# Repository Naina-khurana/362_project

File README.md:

# ProtoPaw (ECE 362, Team 72)

Wearable glove (flex sensor + MPU6050) that drives a 3D-printed robotic finger with an MG90S servo, with live telemetry on the TFT LCD. Runs on the Purdue Proton (RP2350B), PlatformIO + Pico SDK.

## Layout

| File | What it does |
|---|---|
| `include/pins.h` | Shared pin map. Change pins here only |
| `src/flex.c` | ADC driver for the flex sensor |
| `src/servo.c` | PWM driver for the servo |
| `src/imu.c` | I2C driver for the MPU6050, pitch/roll with a complementary filter |
| `src/tft.c` | SPI display, wraps the course `lcd.c` library |
| `src/button.c` | GPIO mode button with debounce |
| `src/main.c` | Main loop, FLEX and TILT modes |

## TFT library setup

Copy `lcd.c` into `src/` and `lcd.h` into `include/` from the course project-lcd zip. In `lcd.c`, replace the three `x` defines with

```c
#include "pins.h"
#define CS_NUM    PIN_CS
#define DC_NUM    PIN_DC
#define RESET_NUM PIN_nRESET
```

Until those files are added, `tft.c` builds as empty stubs so everything else still runs.

## Pin map

| Device | Signal | Pin | Peripheral |
|---|---|---|---|
| Flex sensor | Divider midpoint | GP40 | ADC0 |
| MPU6050 | SDA / SCL | GP4 / GP5 | I2C0 |
| TFT LCD | SCK / SDI | GP10 / GP11 | SPI1 |
| TFT LCD | CS / DC / RESET | GP12 / GP13 / GP14 | GPIO |
| MG90S servo | Signal | GP16 | PWM slice 0A |
| Mode button | Onboard | GP21 | GPIO |

Do not use GP0/GP1 (debug UART), GP21/GP26 for SPI (button debounce circuitry), or GP22-25 (onboard LEDs) for anything else.

## Power

- Flex divider. 3V3 to flex sensor to GP40 to 47k to GND
- MPU6050. VIN to 3V3
- TFT. 3V3 with 10 uF + 0.1 uF caps at its power pins
- Servo. Separate 5V supply, grounds tied together

## Testing the ADC

Set `TEST_MODE_RAW_ADC` to 1 in `main.c`, upload, open the serial monitor and bend the sensor. The raw value should move smoothly and never sit at 0 or 4095.

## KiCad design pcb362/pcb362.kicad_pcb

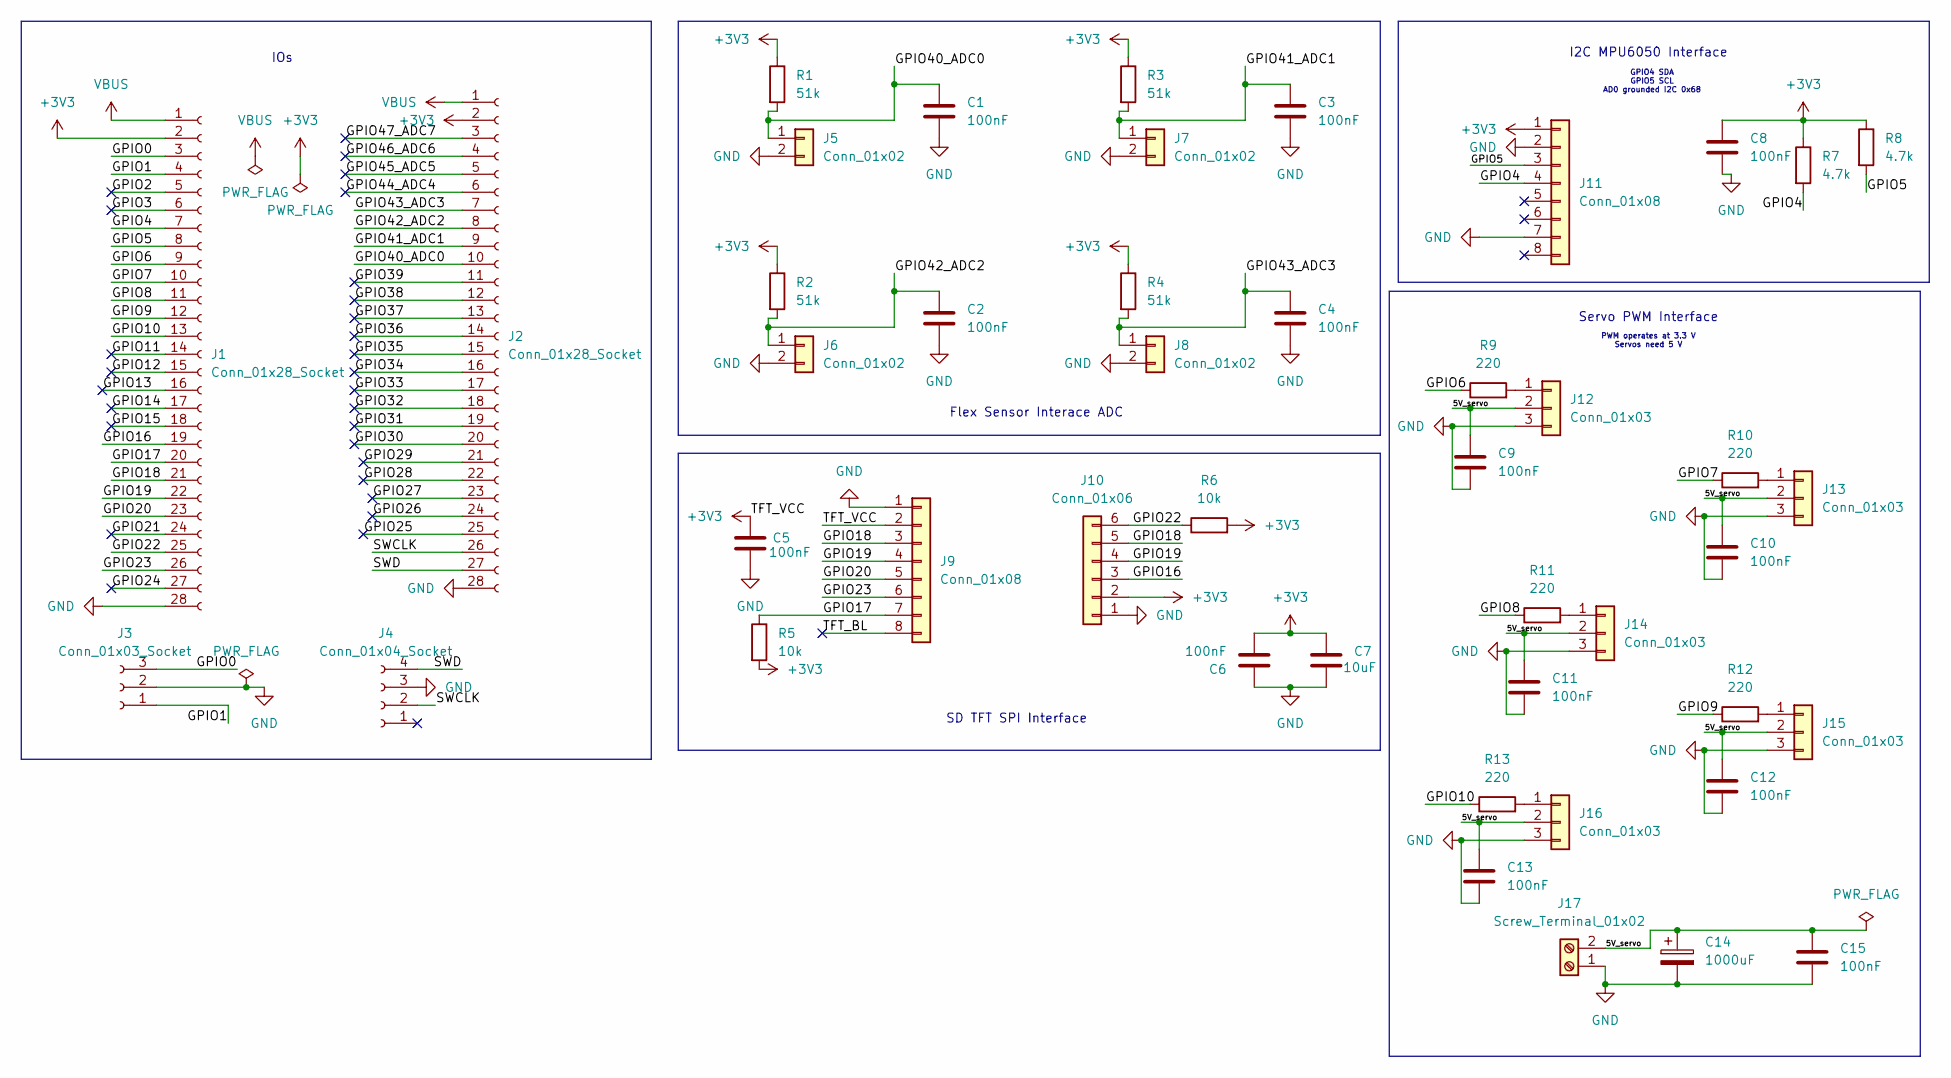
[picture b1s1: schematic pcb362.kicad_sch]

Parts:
C1, C2, C3, C4, C5, C6, C8, C9, C10, C11, C12, C13, C15: 100nF; C_0805_2012Metric
C7: 10uF; C_0805_2012Metric
C14: 1000uF; CP_Radial_D10.0mm_P5.00mm
J1, J2: Conn_01x28_Socket; PinSocket_1x28_P2.54mm_Vertical
J3: Conn_01x03_Socket; PinSocket_1x03_P2.54mm_Vertical
J4: Conn_01x04_Socket; PinSocket_1x04_P2.54mm_Vertical
J5, J6, J7, J8: Conn_01x02; PinHeader_1x02_P2.54mm_Vertical
J9, J11: Conn_01x08; PinHeader_1x08_P2.54mm_Vertical
J10: Conn_01x06; PinHeader_1x06_P2.54mm_Vertical
J12, J13, J14, J15, J16: Conn_01x03; PinHeader_1x03_P2.54mm_Vertical
J17: Screw_Terminal_01x02; TerminalBlock_bornier-2_P5.08mm
R1, R2, R3, R4: 51k; R_0805_2012Metric
R5, R6: 10k; R_0805_2012Metric
R7, R8: 4.7k; R_0805_2012Metric
R9, R10, R11, R12, R13: 220; R_0805_2012Metric

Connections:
+3V3: C5.1, C6.2, C7.2, C8.1, J1.2, J2.2, J9.2, J10.2, J11.1, R1.1, R2.1, R3.1, R4.1, R5.2, R6.2, R7.1, R8.1
/5V_servo: C9.1, C10.1, C11.1, C12.1, C13.1, C14.1, C15.1, J12.2, J13.2, J14.2, J15.2, J16.2, J17.2
/GPIO0: J1.3, J3.3
/GPIO1: J1.4, J3.1
/GPIO2: J1.5
/GPIO3: J1.6
/GPIO4: J1.7, J11.4, R7.2
/GPIO5: J1.8, J11.3, R8.2
/GPIO6: J1.9, R9.1
/GPIO7: J1.10, R10.1
/GPIO8: J1.11, R11.1
/GPIO9: J1.12, R12.1
/GPIO10: J1.13, R13.1
/GPIO11: J1.14
/GPIO12: J1.15
/GPIO13: J1.16
/GPIO14: J1.17
/GPIO15: J1.18
/GPIO16: J1.19, J10.3
/GPIO17: J1.20, J9.7, R5.1
/GPIO18: J1.21, J9.3, J10.5
/GPIO19: J1.22, J9.4, J10.4
/GPIO20: J1.23, J9.5
/GPIO21: J1.24
/GPIO22: J1.25, J10.6, R6.1
/GPIO23: J1.26, J9.6
/GPIO24: J1.27
/GPIO25: J2.25
/GPIO26: J2.24
/GPIO27: J2.23
/GPIO28: J2.22
/GPIO29: J2.21
/GPIO30: J2.20
/GPIO31: J2.19
/GPIO32: J2.18
/GPIO33: J2.17
/GPIO34: J2.16
/GPIO35: J2.15
/GPIO36: J2.14
/GPIO37: J2.13
/GPIO38: J2.12
/GPIO39: J2.11
/GPIO40_ADC0: C1.1, J2.10, J5.1, R1.2
/GPIO41_ADC1: C3.1, J2.9, J7.1, R3.2
/GPIO42_ADC2: C2.1, J2.8, J6.1, R2.2
/GPIO43_ADC3: C4.1, J2.7, J8.1, R4.2
/GPIO44_ADC4: J2.6
/GPIO45_ADC5: J2.5
/GPIO46_ADC6: J2.4
/GPIO47_ADC7: J2.3
/SWCLK: J2.26, J4.2
/SWD: J2.27, J4.4
/TFT_BL: J9.8
GND: C1.2, C2.2, C3.2, C4.2, C5.2, C6.1, C7.1, C8.2, C9.2, C10.2, C11.2, C12.2, C13.2, C14.2, C15.2, J1.28, J2.28, J3.2, J4.3, J5.2, J6.2, J7.2, J8.2, J9.1, J10.1, J11.2, J11.7, J12.3, J13.3, J14.3, J15.3, J16.3, J17.1
unnamed: J12.1, R9.2
unnamed: J13.1, R10.2
unnamed: J14.1, R11.2
unnamed: J15.1, R12.2
unnamed: J16.1, R13.2
VBUS: J1.1, J2.1

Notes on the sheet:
I2C MPU6050 Interface
Servo PWM Interface
PWM operates at 3.3 V Servos need 5 V
IOs
Flex Sensor Interace ADC
SD TFT SPI Interface
GPIO4 SDA GPIO5 SCL AD0 grounded I2C 0x68

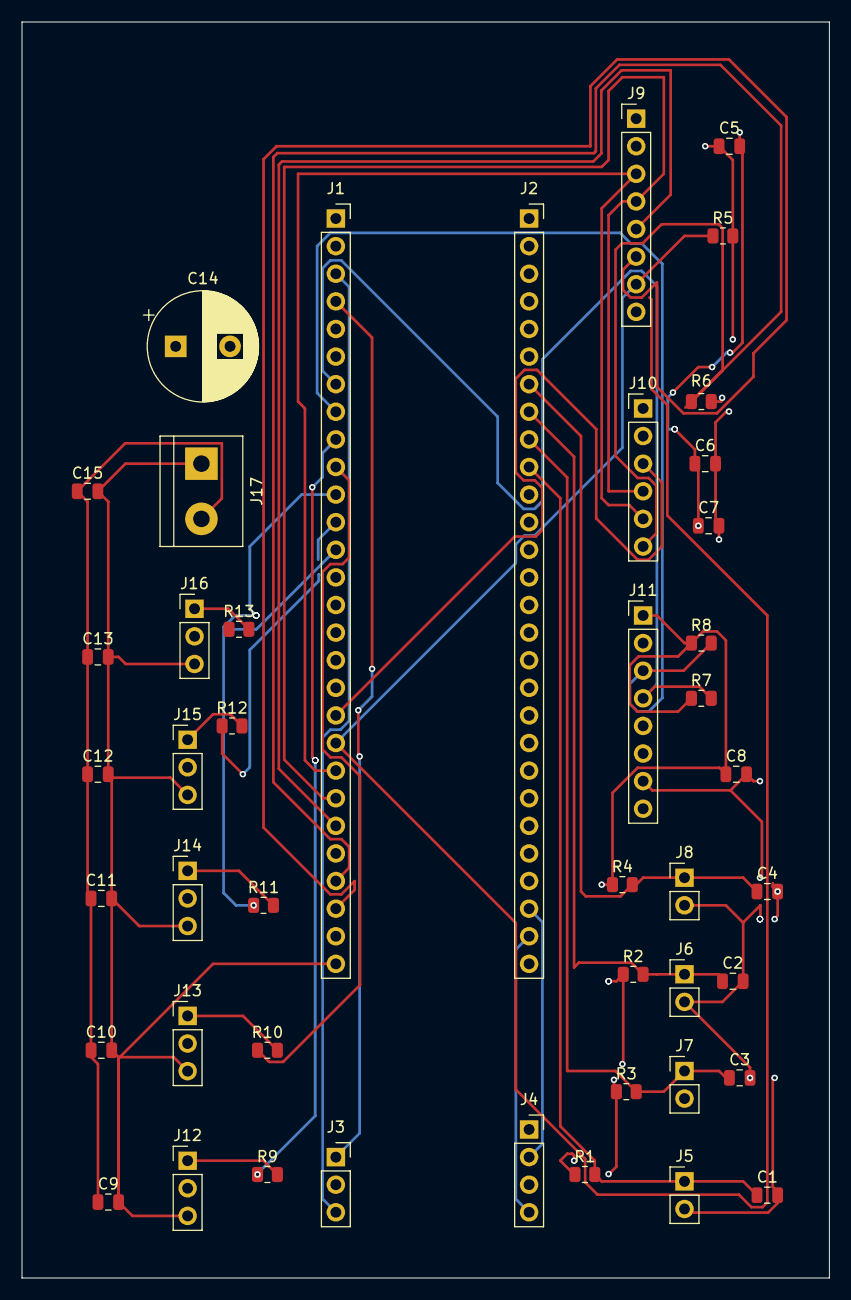
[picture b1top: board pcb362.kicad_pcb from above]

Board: 4 copper layers, 74.3 x 115.6 mm, 45 parts (0 on the bottom side), 31 nets.
